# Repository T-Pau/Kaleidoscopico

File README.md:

# Kaleidoscopico

[Kaleidoscopico](https://www.linusakesson.net/scene/kaleidoscopico/index.php) is a microcontroller demo by Linus Åkesson that runs on a Raspberry Pi Pico 2. It placed 2nd in the Wild compo at Revision 2025.

This is a small PCB so you can assemble the required hardware cleanly and easily.

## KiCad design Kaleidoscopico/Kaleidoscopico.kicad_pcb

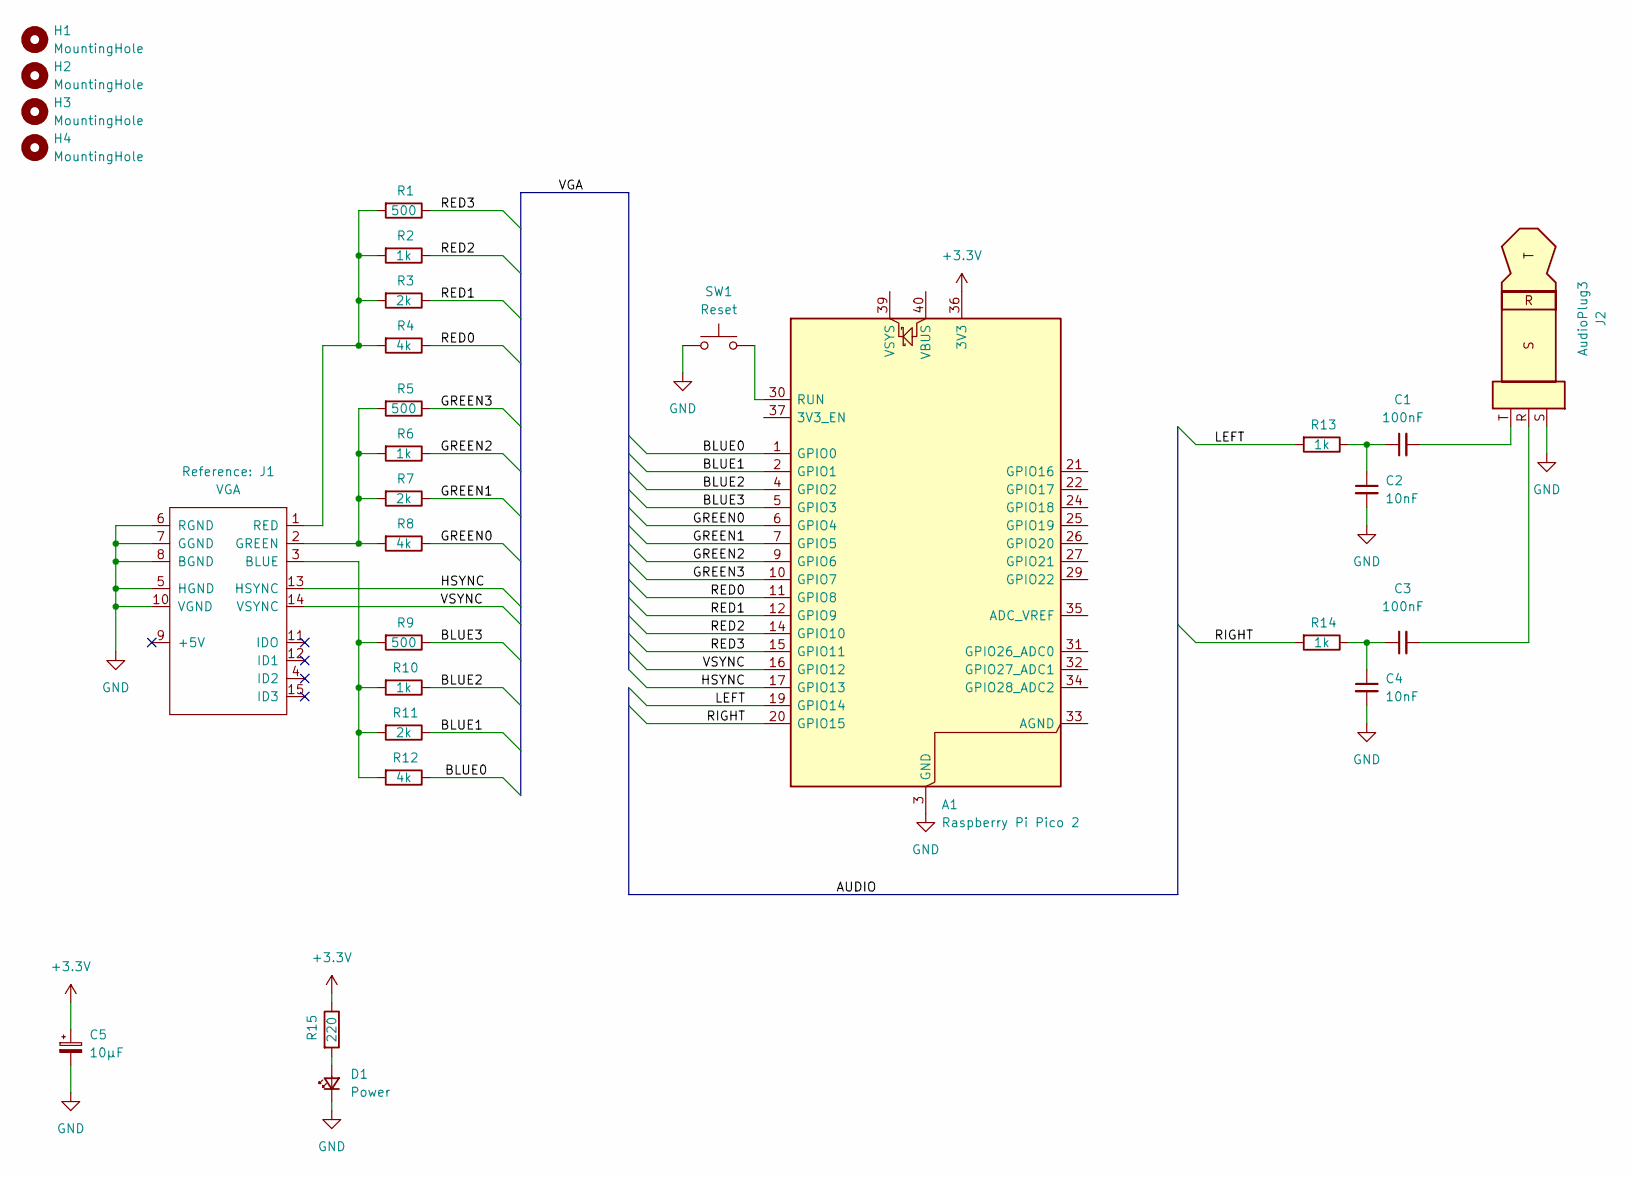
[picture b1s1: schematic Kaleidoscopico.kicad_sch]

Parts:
A1: Raspberry Pi Pico 2; RaspberryPi_Pico_Common_Unspecified
C1, C3: 100nF; C_Disc_D5.0mm_W2.5mm_P5.00mm
C2, C4: 10nF; C_Disc_D5.0mm_W2.5mm_P5.00mm
C5: 10µF; CP_Radial_D5.0mm_P2.00mm
D1: Power; LED_D5.0mm
H1, H2, H3, H4: MountingHole; MountingHole_3.2mm_M3
J1: VGA; DSUB-15-HD_Socket_Horizontal_P2.29x2.54mm_EdgePinOffset8.35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
J2: AudioPlug3; Jack_3.5mm_CUI_SJ1-3515N_Horizontal
R1, R5, R9: 500; R_Axial_DIN0207_L6.3mm_D2.5mm_P10.16mm_Horizontal
R2, R6, R10, R13, R14: 1k; R_Axial_DIN0207_L6.3mm_D2.5mm_P10.16mm_Horizontal
R3, R7, R11: 2k; R_Axial_DIN0207_L6.3mm_D2.5mm_P10.16mm_Horizontal
R4, R8, R12: 4k; R_Axial_DIN0207_L6.3mm_D2.5mm_P10.16mm_Horizontal
R15: 220; R_Axial_DIN0207_L6.3mm_D2.5mm_P10.16mm_Horizontal
SW1: Reset; SW_PUSH_6mm

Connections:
+3.3V: A1.36 (3V3), C5.1, R15.1
/BLUE0: A1.1 (GPIO0), R12.1
/BLUE1: A1.2 (GPIO1), R11.1
/BLUE2: A1.4 (GPIO2), R10.1
/BLUE3: A1.5 (GPIO3), R9.1
/GREEN0: A1.6 (GPIO4), R8.1
/GREEN1: A1.7 (GPIO5), R7.1
/GREEN2: A1.9 (GPIO6), R6.1
/GREEN3: A1.10 (GPIO7), R5.1
/HSYNC: A1.17 (GPIO13), J1.13 (HSYNC)
/LEFT: A1.19 (GPIO14), R13.2
/RED0: A1.11 (GPIO8), R4.1
/RED1: A1.12 (GPIO9), R3.1
/RED2: A1.14 (GPIO10), R2.1
/RED3: A1.15 (GPIO11), R1.1
/RIGHT: A1.20 (GPIO15), R14.2
/VSYNC: A1.16 (GPIO12), J1.14 (VSYNC)
GND: A1.3 (GND), A1.8 (GND), A1.13 (GND), A1.18 (GND), A1.23 (GND), A1.28 (GND), A1.38 (GND), C2.2, C4.2, C5.2, D1.1 (K), J1.5 (HGND), J1.6 (RGND), J1.7 (GGND), J1.8 (BGND), J1.10 (VGND), J2.S, SW1.1
unnamed: A1.30 (RUN), SW1.2
unnamed: C1.1, C2.1, R13.1
unnamed: C1.2, J2.T
unnamed: C3.1, C4.1, R14.1
unnamed: C3.2, J2.R
unnamed: D1.2 (A), R15.2
unnamed: J1.3 (BLUE), R9.2, R10.2, R11.2, R12.2
unnamed: J1.2 (GREEN), R5.2, R6.2, R7.2, R8.2
unnamed: J1.1 (RED), R1.2, R2.2, R3.2, R4.2

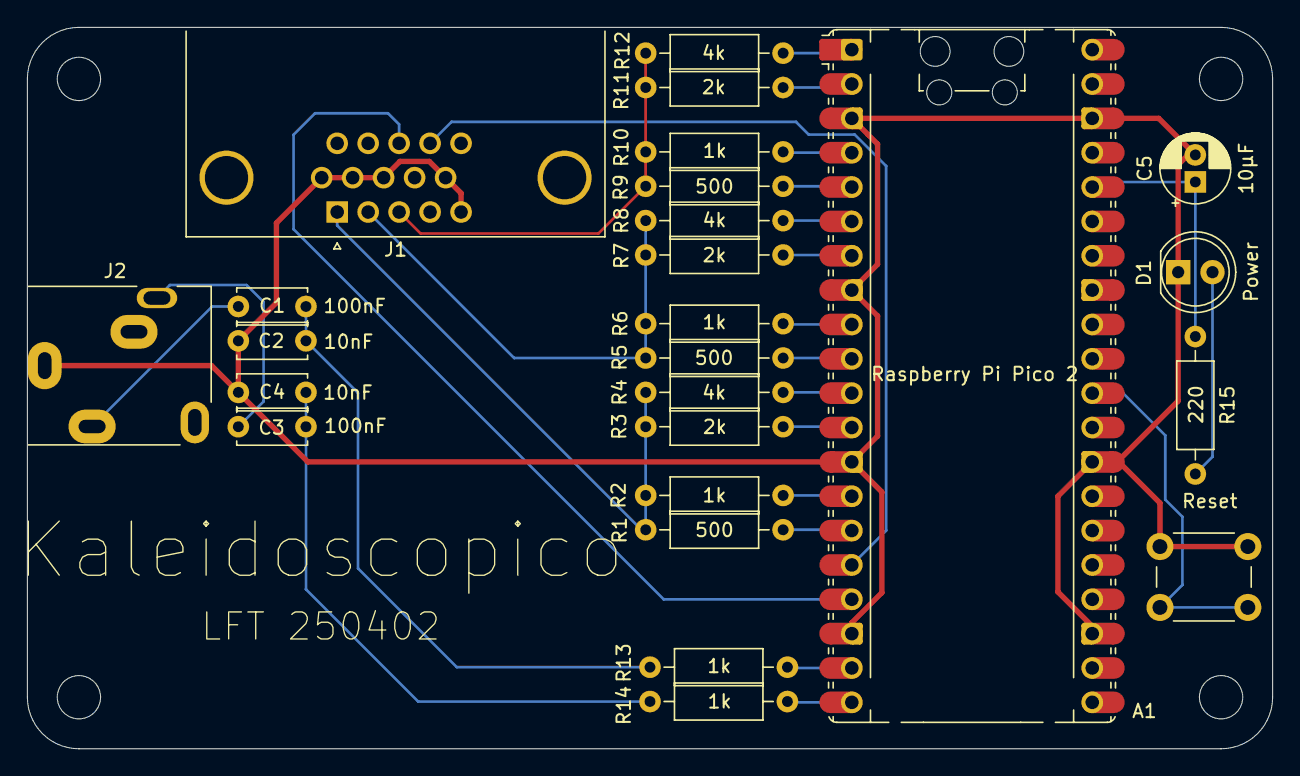
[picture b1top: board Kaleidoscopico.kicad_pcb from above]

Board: 2 copper layers, 92.1 x 53.3 mm, 29 parts (0 on the bottom side), 27 nets.

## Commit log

2025-04-26 PCB done
2025-05-13 Add README.
